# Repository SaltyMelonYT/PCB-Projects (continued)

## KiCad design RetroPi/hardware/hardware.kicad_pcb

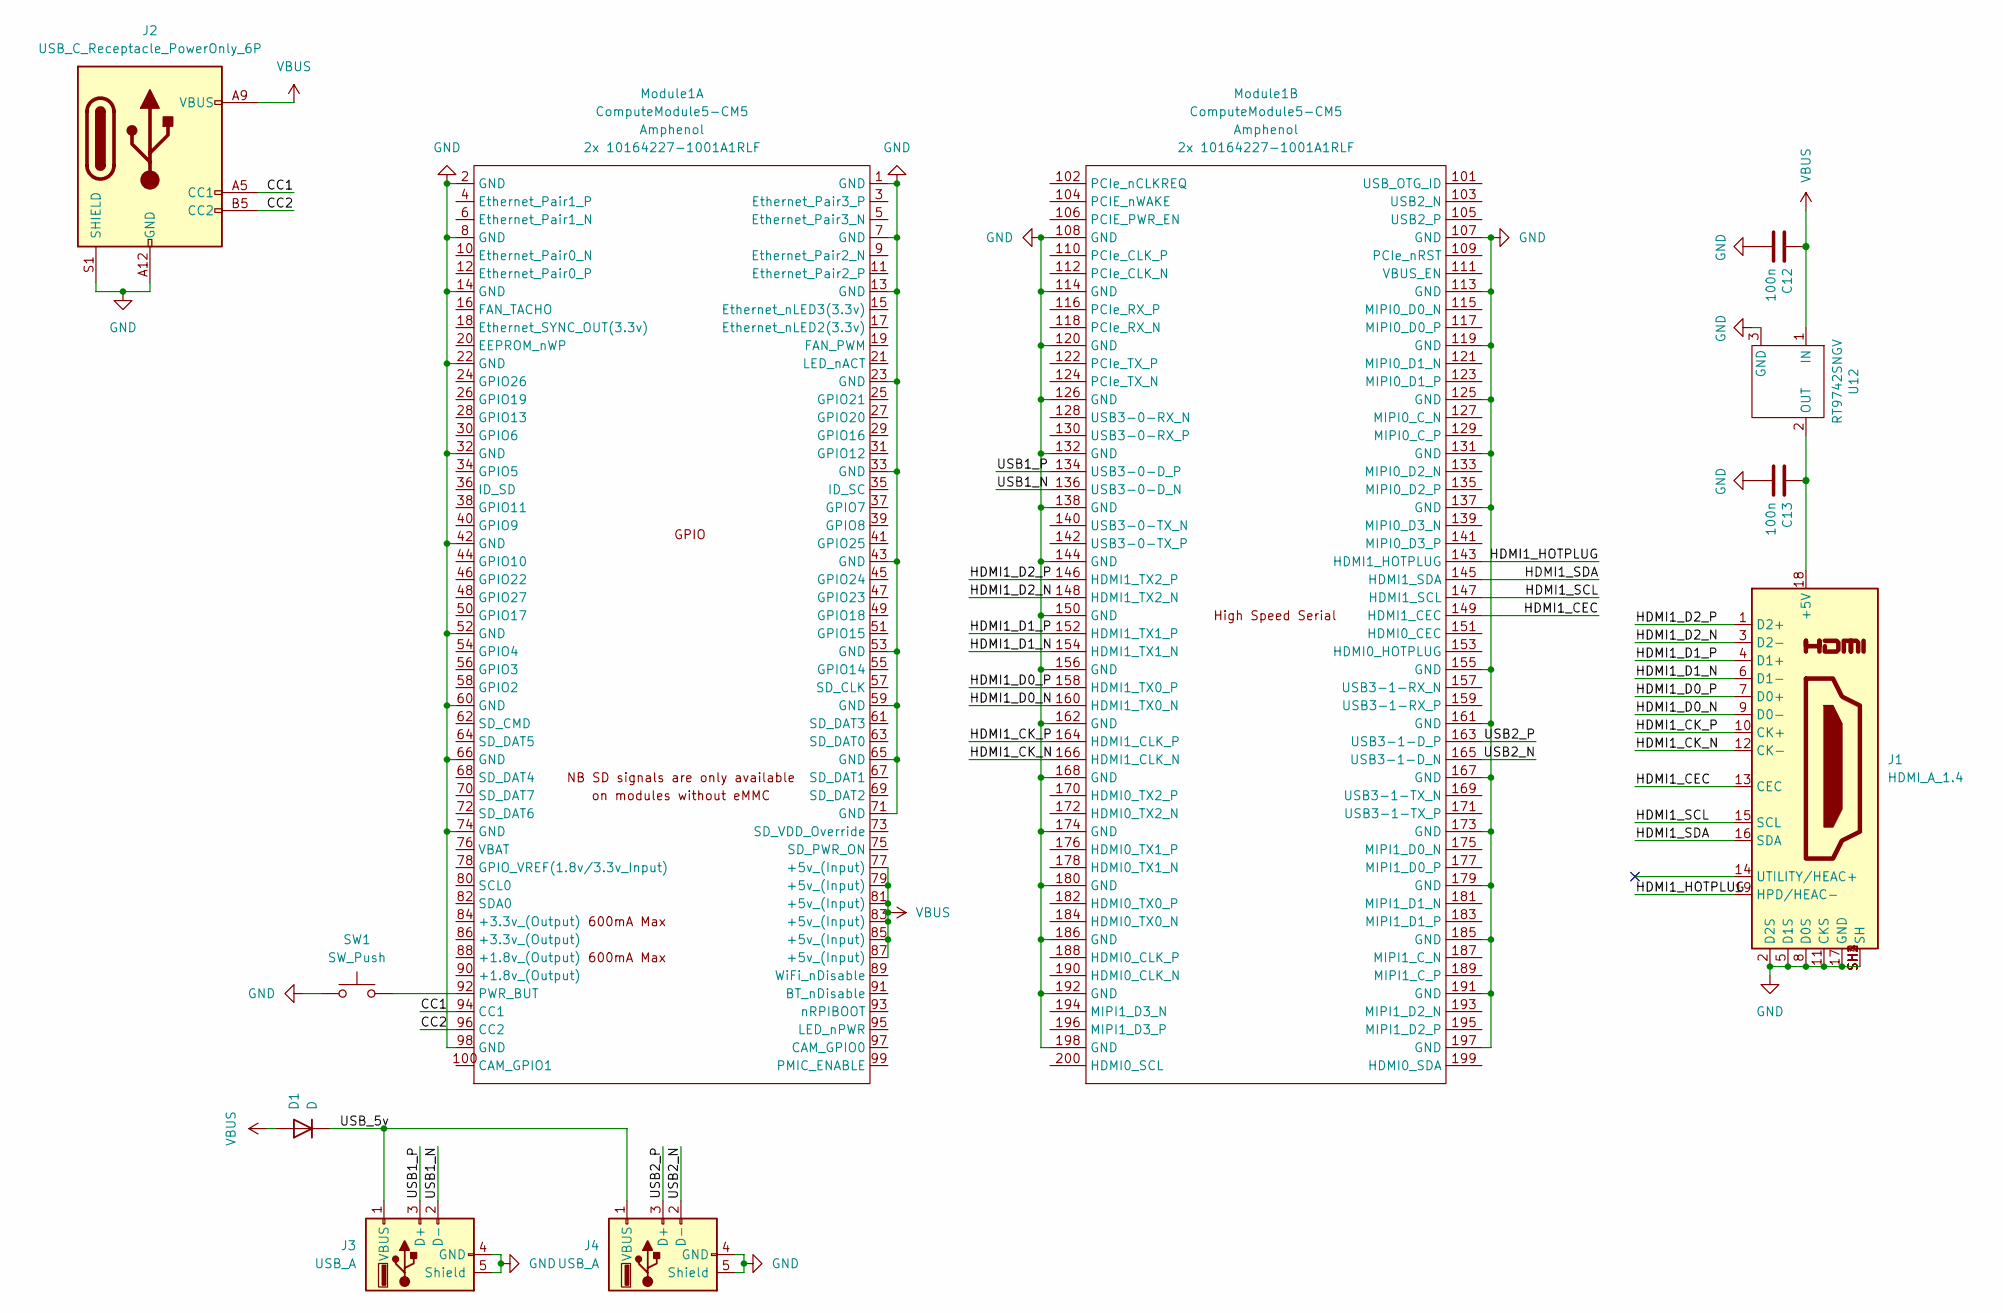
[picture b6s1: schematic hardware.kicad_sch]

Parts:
C12, C13: 100n; C_0402_1005Metric; Part Description 0.1uF 10% 16V Ceramic Capacitor X7R 040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
D1: D; D_2010_5025Metric_Pad1.52x2.65mm_HandSolder
J1: HDMI_A_1.4; HDMI_A_Molex_208658-1001_Horizontal
J2: USB_C_Receptacle_PowerOnly_6P; USB_C_Receptacle_GCT_USB4125-xx-x_6P_TopMnt_Horizontal
J3, J4: USB_A; USB_A_Molex_67643_Horizontal
Module1: ComputeModule5-CM5; Raspberry-Pi-5-Compute-Module
SW1: SW_Push; SW_SPST_B3U-3000P-B
U12: RT9742SNGV; TSOT-23_HandSoldering; Part Description Power Switch/Driver 1:1 N-Channel 500mA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

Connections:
/CC1: J2.A5 (CC1), Module1.94 (CC1)
/CC2: J2.B5 (CC2), Module1.96 (CC2)
/HDMI1_CEC: J1.13 (CEC), Module1.149 (HDMI1_CEC)
/HDMI1_CK_N: J1.12 (CK-), Module1.166 (HDMI1_CLK_N)
/HDMI1_CK_P: J1.10 (CK+), Module1.164 (HDMI1_CLK_P)
/HDMI1_D0_N: J1.9 (D0-), Module1.160 (HDMI1_TX0_N)
/HDMI1_D0_P: J1.7 (D0+), Module1.158 (HDMI1_TX0_P)
/HDMI1_D1_N: J1.6 (D1-), Module1.154 (HDMI1_TX1_N)
/HDMI1_D1_P: J1.4 (D1+), Module1.152 (HDMI1_TX1_P)
/HDMI1_D2_N: J1.3 (D2-), Module1.148 (HDMI1_TX2_N)
/HDMI1_D2_P: J1.1 (D2+), Module1.146 (HDMI1_TX2_P)
/HDMI1_HOTPLUG: J1.19 (HPD/HEAC-), Module1.143 (HDMI1_HOTPLUG)
/HDMI1_SCL: J1.15 (SCL), Module1.147 (HDMI1_SCL)
/HDMI1_SDA: J1.16 (SDA), Module1.145 (HDMI1_SDA)
/USB1_N: J3.2 (D-), Module1.136 (USB3-0-D_N)
/USB1_P: J3.3 (D+), Module1.134 (USB3-0-D_P)
/USB2_N: J4.2 (D-), Module1.165 (USB3-1-D_N)
/USB2_P: J4.3 (D+), Module1.163 (USB3-1-D_P)
/USB_5v: D1.1 (K), J3.1 (VBUS), J4.1 (VBUS)
GND: C12.2, C13.2, J1.2 (D2S), J1.5 (D1S), J1.8 (D0S), J1.11 (CKS), J1.17 (GND), J1.SH1 (SH), J1.SH2 (SH), J1.SH3 (SH), J1.SH4 (SH), J2.A12 (GND), J2.B12 (GND), J2.S1 (SHIELD), J3.4 (GND), J3.5 (Shield), J4.4 (GND), J4.5 (Shield), Module1.1 (GND), Module1.2 (GND), Module1.7 (GND), Module1.8 (GND), Module1.13 (GND), Module1.14 (GND), Module1.22 (GND), Module1.23 (GND), Module1.32 (GND), Module1.33 (GND), Module1.42 (GND), Module1.43 (GND), Module1.52 (GND), Module1.53 (GND), Module1.59 (GND), Module1.60 (GND), Module1.65 (GND), Module1.66 (GND), Module1.71 (GND), Module1.74 (GND), Module1.98 (GND), Module1.107 (GND), Module1.108 (GND), Module1.113 (GND), Module1.114 (GND), Module1.119 (GND), Module1.120 (GND), Module1.125 (GND), Module1.126 (GND), Module1.131 (GND), Module1.132 (GND), Module1.137 (GND), Module1.138 (GND), Module1.144 (GND), Module1.150 (GND), Module1.155 (GND), Module1.156 (GND), Module1.161 (GND), Module1.162 (GND), Module1.167 (GND), Module1.168 (GND), Module1.173 (GND), Module1.174 (GND), Module1.179 (GND), Module1.180 (GND), Module1.185 (GND), Module1.186 (GND), Module1.191 (GND), Module1.192 (GND), Module1.197 (GND), Module1.198 (GND), SW1.1, U12.3 (GND)
unnamed: C13.1, J1.18 (+5V), U12.2 (OUT)
unnamed: Module1.92 (PWR_BUT), SW1.2
VBUS: C12.1, D1.2 (A), J2.A9 (VBUS), J2.B9 (VBUS), Module1.77 (+5v_(Input)), Module1.79 (+5v_(Input)), Module1.81 (+5v_(Input)), Module1.83 (+5v_(Input)), Module1.85 (+5v_(Input)), Module1.87 (+5v_(Input)), U12.1 (IN)

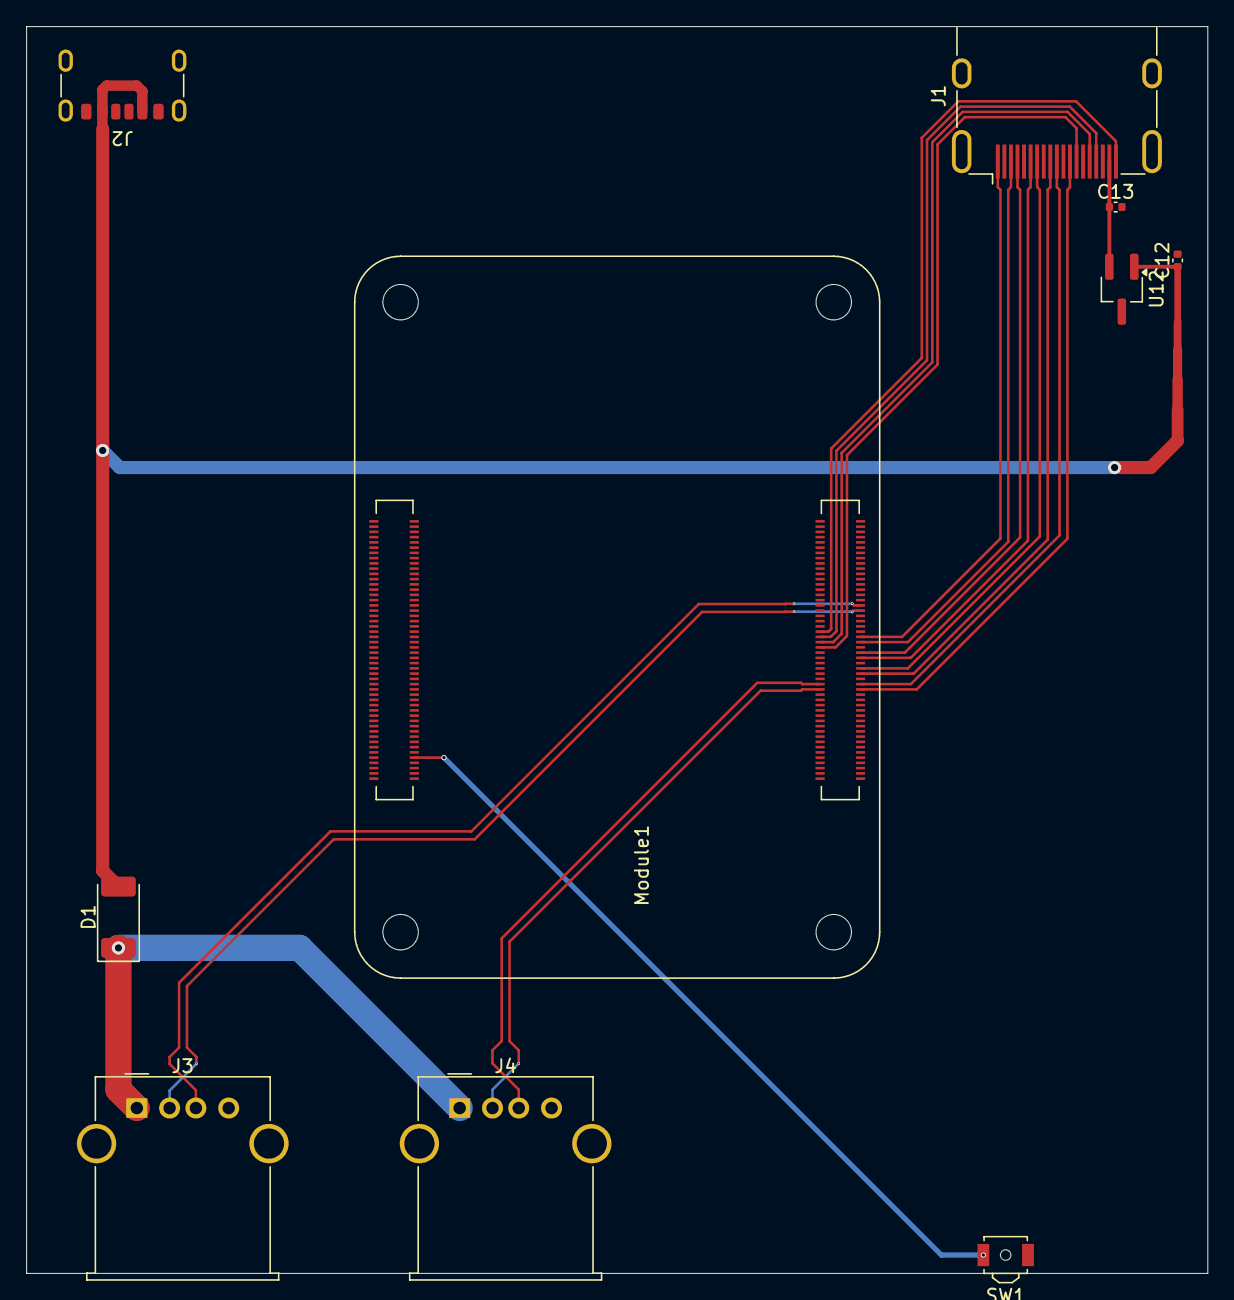
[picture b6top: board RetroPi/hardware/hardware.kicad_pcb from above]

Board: 2 copper layers, 90.0 x 95.0 mm, 10 parts (0 on the bottom side), 23 nets.
